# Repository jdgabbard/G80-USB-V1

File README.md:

# G80-USB V1
 G80-USB v1.0 SBC

The G80-USB Micro SBC.  The second iteration of the G80 Computer family, this computer made a change to it's communication by allowing for RS-232 or USB Serial interfaces to communicate with the computer.

The source code for the firmware can be found here: https://github.com/jdgabbard/z80-G-DOS

Or you can download previous version of the software in the downloads section of my website:  www.retrodepot.net

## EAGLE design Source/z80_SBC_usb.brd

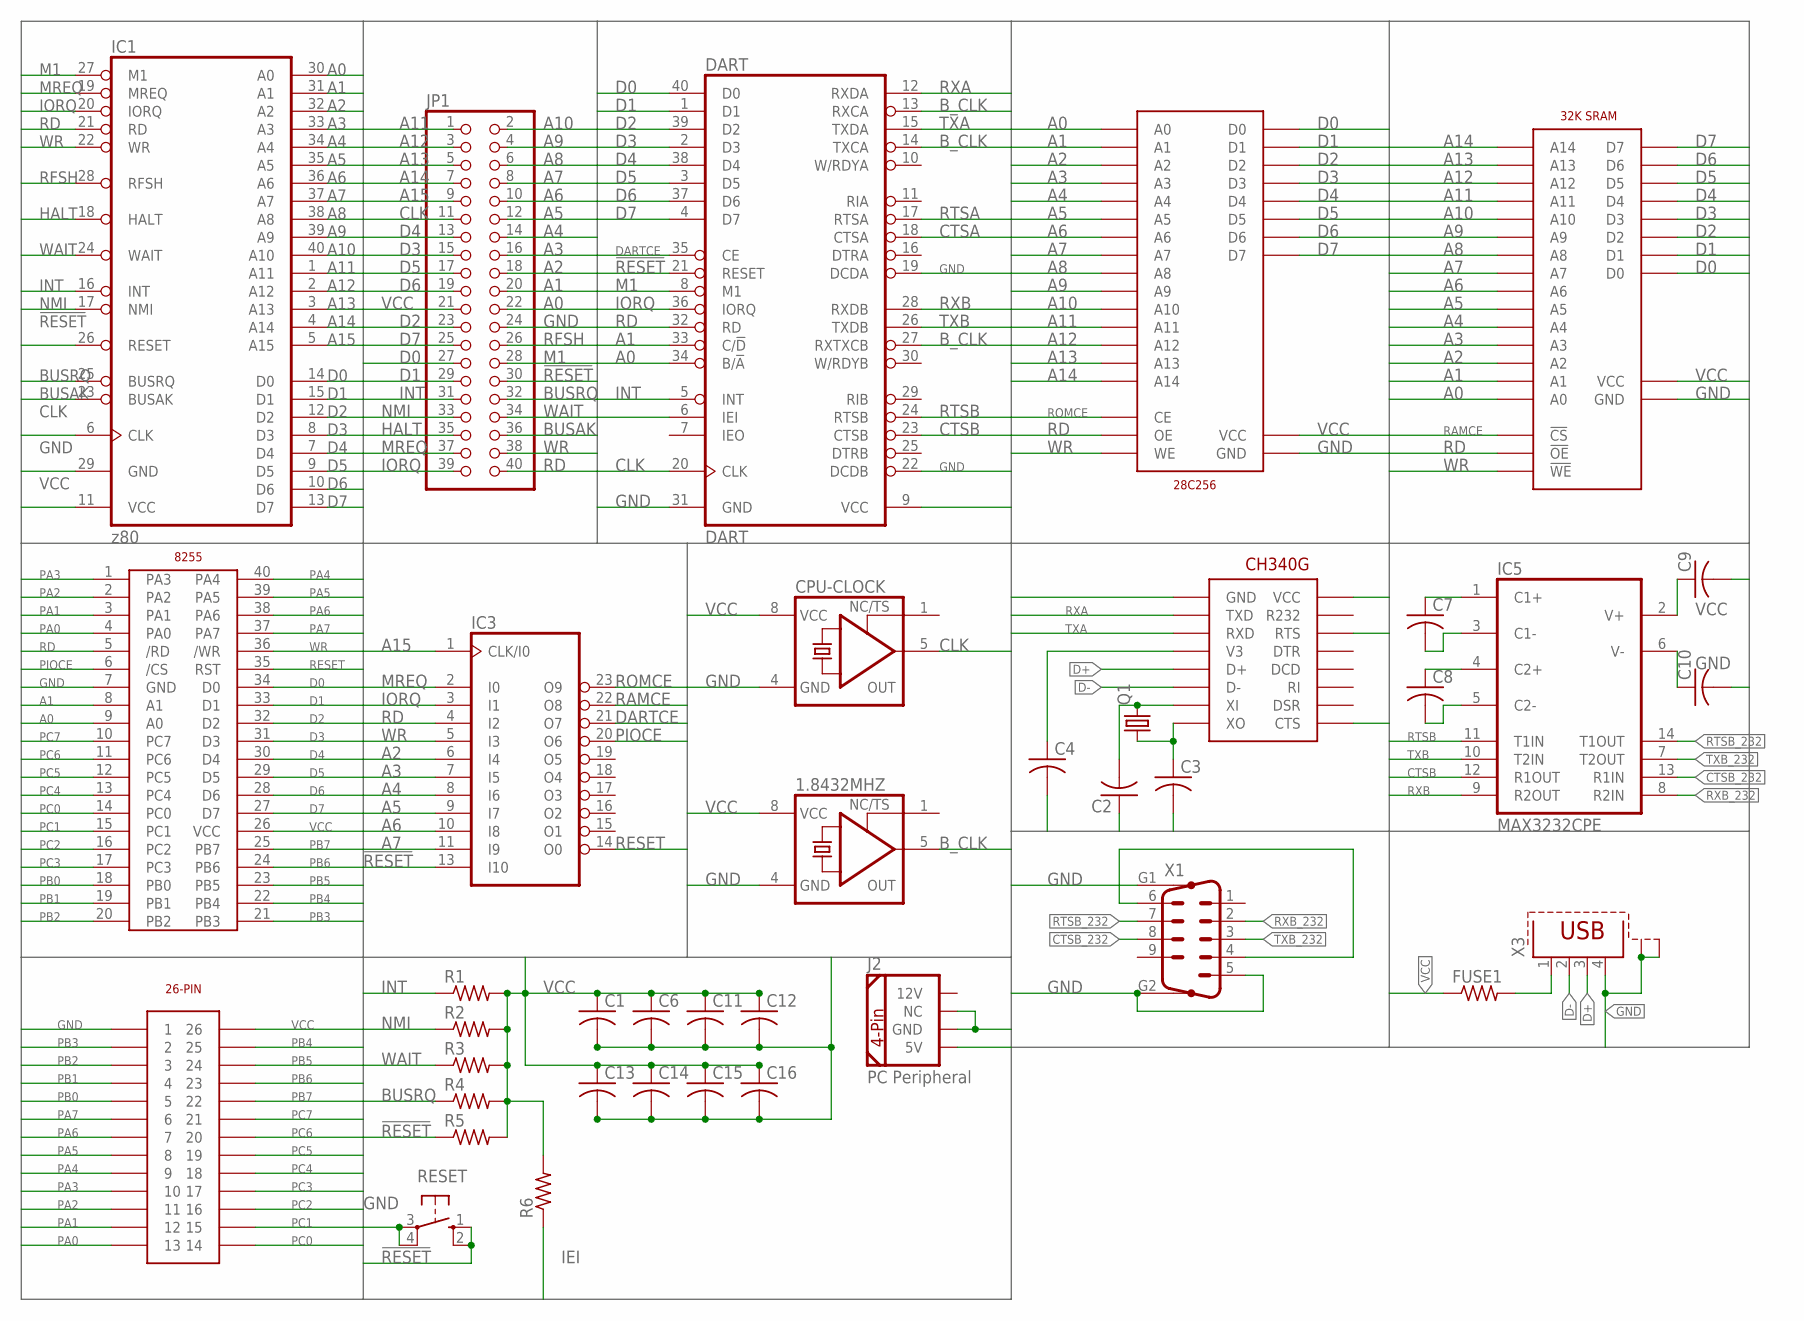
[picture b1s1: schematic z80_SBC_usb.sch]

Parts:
1.8432MHZ: XO-8; DIL08S
28C256: 28C256; DIP28
C1, C4, C6, C7, C8, C9, C10, C11, C12, C13, C14, C15, C16: C-USC0805; C0805
C2, C3: C-US050-024X044; C050-024X044
CPU-CLOCK: XO-8; DIL08S
DART: DART; DIL40
FUSE1: R-US_R1206W; R1206W
IC1: z80; DIL40
IC3: 22V10; DIL24-3
IC4: 8255
IC5: MAX3232CPE; DIL16
IC6: 32K SRAM; DIP28-300
IC7: CH340G; SO16
J1: SOCKET-DIP26
J2: PC Peripheral; COMPUTER-PERIPHERAL-POWER
JP1: PINHD-2X20; 2X20
Q1: CRYSTALHC49S; HC49/S
R1, R2, R3, R4, R5, R6: R-US_M0805; M0805
RESET: 10-XX; B3F-10XX
X1: M09HP
X3: PN61729-S

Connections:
!RESET: DART.21 (RESET), IC1.26 (RESET), IC3.13 (I10), JP1.30, R5.1, RESET.1 (S), RESET.2 (S1)
A0: 28C256.P$10 (A0), DART.34 (B/!A), IC1.30 (A0), IC4.9 (A0), IC6.P$10 (A0), JP1.22
A1: 28C256.P$9 (A1), DART.33 (C/!D), IC1.31 (A1), IC4.8 (A1), IC6.P$9 (A1), JP1.20
A2: 28C256.P$8 (A2), IC1.32 (A2), IC3.6 (I4), IC6.P$8 (A2), JP1.18
A3: 28C256.P$7 (A3), IC1.33 (A3), IC3.7 (I5), IC6.P$7 (A3), JP1.16
A4: 28C256.P$6 (A4), IC1.34 (A4), IC3.8 (I6), IC6.P$6 (A4), JP1.14
A5: 28C256.P$5 (A5), IC1.35 (A5), IC3.9 (I7), IC6.P$5 (A5), JP1.12
A6: 28C256.P$4 (A6), IC1.36 (A6), IC3.10 (I8), IC6.P$4 (A6), JP1.10
A7: 28C256.P$3 (A7), IC1.37 (A7), IC3.11 (I9), IC6.P$3 (A7), JP1.8
A8: 28C256.P$25 (A8), IC1.38 (A8), IC6.P$25 (A8), JP1.6
A9: 28C256.P$24 (A9), IC1.39 (A9), IC6.P$24 (A9), JP1.4
A10: 28C256.P$21 (A10), IC1.40 (A10), IC6.P$21 (A10), JP1.2
A11: 28C256.P$23 (A11), IC1.1 (A11), IC6.P$23 (A11), JP1.1
A12: 28C256.P$2 (A12), IC1.2 (A12), IC6.P$2 (A12), JP1.3
A13: 28C256.P$26 (A13), IC1.3 (A13), IC6.P$26 (A13), JP1.5
A14: 28C256.P$1 (A14), IC1.4 (A14), IC6.P$1 (A14), JP1.7
A15: IC1.5 (A15), IC3.1 (CLK/I0), JP1.9
BUSAK: IC1.23 (BUSAK), JP1.36
BUSRQ: IC1.25 (BUSRQ), JP1.32, R4.1
B_CLK: 1.8432MHZ.5 (OUT), DART.13 (RXCA), DART.14 (TXCA), DART.27 (RXTXCB)
CLK: CPU-CLOCK.5 (OUT), DART.20 (CLK), IC1.6 (CLK), JP1.11
CTSA: DART.18 (CTSA), IC7.14 (RTS)
CTSB: DART.23 (CTSB), IC5.12 (R1OUT)
CTSB_232: IC5.13 (R1IN), X1.8
D0: 28C256.P$11 (D0), DART.40 (D0), IC1.14 (D0), IC4.34 (D0), IC6.P$11 (D0), JP1.27
D1: 28C256.P$12 (D1), DART.1 (D1), IC1.15 (D1), IC4.33 (D1), IC6.P$12 (D1), JP1.29
D2: 28C256.P$13 (D2), DART.39 (D2), IC1.12 (D2), IC4.32 (D2), IC6.P$13 (D2), JP1.23
D3: 28C256.P$15 (D3), DART.2 (D3), IC1.8 (D3), IC4.31 (D3), IC6.P$15 (D3), JP1.15
D4: 28C256.P$16 (D4), DART.38 (D4), IC1.7 (D4), IC4.30 (D4), IC6.P$16 (D4), JP1.13
D5: 28C256.P$17 (D5), DART.3 (D5), IC1.9 (D5), IC4.29 (D5), IC6.P$17 (D5), JP1.17
D6: 28C256.P$18 (D6), DART.37 (D6), IC1.10 (D6), IC4.28 (D6), IC6.P$18 (D6), JP1.19
D7: 28C256.P$19 (D7), DART.4 (D7), IC1.13 (D7), IC4.27 (D7), IC6.P$19 (D7), JP1.25
D+: IC7.5 (D+), X3.3
D-: IC7.6 (D-), X3.2
DARTCE: DART.35 (CE), IC3.21 (O7)
GND: 1.8432MHZ.4 (GND), 28C256.P$14 (GND), C1.2, C2.1, C3.2, C4.2, C6.2, C10.2, C11.2, C12.2, C13.2, C14.2, C15.2, C16.2, CPU-CLOCK.4 (GND), DART.19 (DCDA), DART.22 (DCDB), DART.31 (GND), IC1.29 (GND), IC3.12 (GND), IC4.7 (GND), IC5.15 (GND), IC6.P$14 (GND), IC7.1 (GND), J1.P$1 (1), J2.GND, J2.NC, JP1.24, RESET.3, RESET.4 (P1), X1.5, X1.G1, X1.G2, X3.4, X3.S1, X3.S2
HALT: IC1.18 (HALT), JP1.35
IEI: DART.6 (IEI), R6.1
INT: DART.5 (INT), IC1.16 (INT), JP1.31, R1.1
IORQ: DART.36 (IORQ), IC1.20 (IORQ), IC3.3 (I1), JP1.39
M1: DART.8 (M1), IC1.27 (M1), JP1.28
MREQ: IC1.19 (MREQ), IC3.2 (I0), JP1.37
unnamed: C7.1, IC5.1 (C1+)
unnamed: C8.1, IC5.4 (C2+)
unnamed: C8.2, IC5.5 (C2-)
unnamed: C7.2, IC5.3 (C1-)
unnamed: C9.1, IC5.2 (V+)
unnamed: C10.1, IC5.6 (V-)
unnamed: C2.2, IC7.7 (XI), Q1.2
unnamed: C3.1, IC7.8 (XO), Q1.1
unnamed: FUSE1.2, X3.1
unnamed: C4.1, IC7.4 (V3)
unnamed: X1.4, X1.6
NMI: IC1.17 (NMI), JP1.33, R2.1
PA0: IC4.4 (PA0), J1.P$13 (13)
PA1: IC4.3 (PA1), J1.P$12 (12)
PA2: IC4.2 (PA2), J1.P$11 (11)
PA3: IC4.1 (PA3), J1.P$10 (10)
PA4: IC4.40 (PA4), J1.P$9 (9)
PA5: IC4.39 (PA5), J1.P$8 (8)
PA6: IC4.38 (PA6), J1.P$7 (7)
PA7: IC4.37 (PA7), J1.P$6 (6)
PB0: IC4.18 (PB0), J1.P$5 (5)
PB1: IC4.19 (PB1), J1.P$4 (4)
PB2: IC4.20 (PB2), J1.P$3 (3)
PB3: IC4.21 (PB3), J1.P$2 (2)
PB4: IC4.22 (PB4), J1.P$25 (25)
PB5: IC4.23 (PB5), J1.P$24 (24)
PB6: IC4.24 (PB6), J1.P$23 (23)
PB7: IC4.25 (PB7), J1.P$22 (22)
PC0: IC4.14 (PC0), J1.P$14 (14)
PC1: IC4.15 (PC1), J1.P$15 (15)
PC2: IC4.16 (PC2), J1.P$16 (16)
PC3: IC4.17 (PC3), J1.P$17 (17)
PC4: IC4.13 (PC4), J1.P$18 (18)
PC5: IC4.12 (PC5), J1.P$19 (19)
PC6: IC4.11 (PC6), J1.P$20 (20)
PC7: IC4.10 (PC7), J1.P$21 (21)
PIOCE: IC3.20 (O6), IC4.6 (/CS)
RAMCE: IC3.22 (O8), IC6.P$20 (!CS)
RD: 28C256.P$22 (OE), DART.32 (RD), IC1.21 (RD), IC3.4 (I2), IC4.5 (/RD), IC6.P$22 (!OE), JP1.40
RESET: IC3.14 (O0), IC4.35 (RST)
RFSH: IC1.28 (RFSH), JP1.26
ROMCE: 28C256.P$20 (CE), IC3.23 (O9)
RTSA: DART.17 (RTSA), IC7.9 (CTS)
RTSB: DART.24 (RTSB), IC5.11 (T1IN)
RTSB_232: IC5.14 (T1OUT), X1.7
RXA: DART.12 (RXDA), IC7.2 (TXD)
RXB: DART.28 (RXDB), IC5.9 (R2OUT)
RXB_232: IC5.8 (R2IN), X1.2
TXA: DART.15 (TXDA), IC7.3 (RXD)
TXB: DART.26 (TXDB), IC5.10 (T2IN)
TXB_232: IC5.7 (T2OUT), X1.3
VCC: 1.8432MHZ.8 (VCC), 28C256.P$28 (VCC), C1.1, C6.1, C9.2, C11.1, C12.1, C13.1, C14.1, C15.1, C16.1, CPU-CLOCK.8 (VCC), DART.9 (VCC), FUSE1.1, IC1.11 (VCC), IC3.24 (VCC), IC4.26 (VCC), IC5.16 (VCC), IC6.P$28 (VCC), IC7.16 (VCC), J1.P$26 (26), J2.5V, JP1.21, R1.2, R2.2, R3.2, R4.2, R5.2, R6.2
WAIT: IC1.24 (WAIT), JP1.34, R3.1
WR: 28C256.P$27 (WE), IC1.22 (WR), IC3.5 (I3), IC4.36 (/WR), IC6.P$27 (!WE), JP1.38

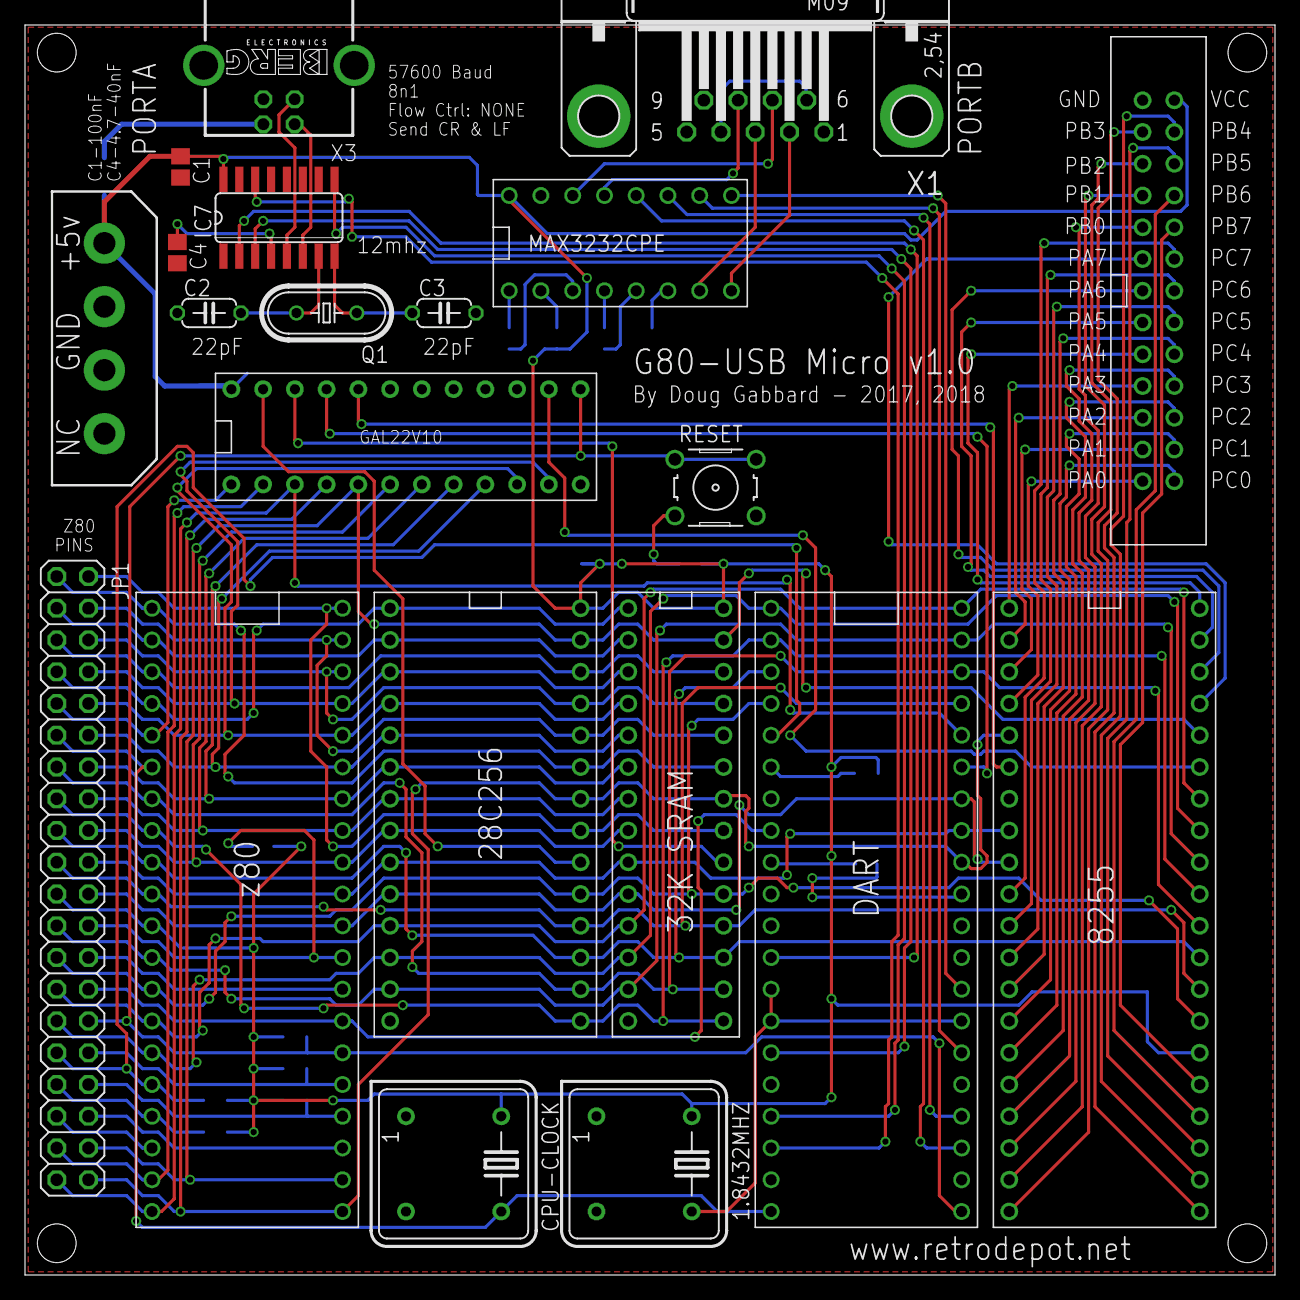
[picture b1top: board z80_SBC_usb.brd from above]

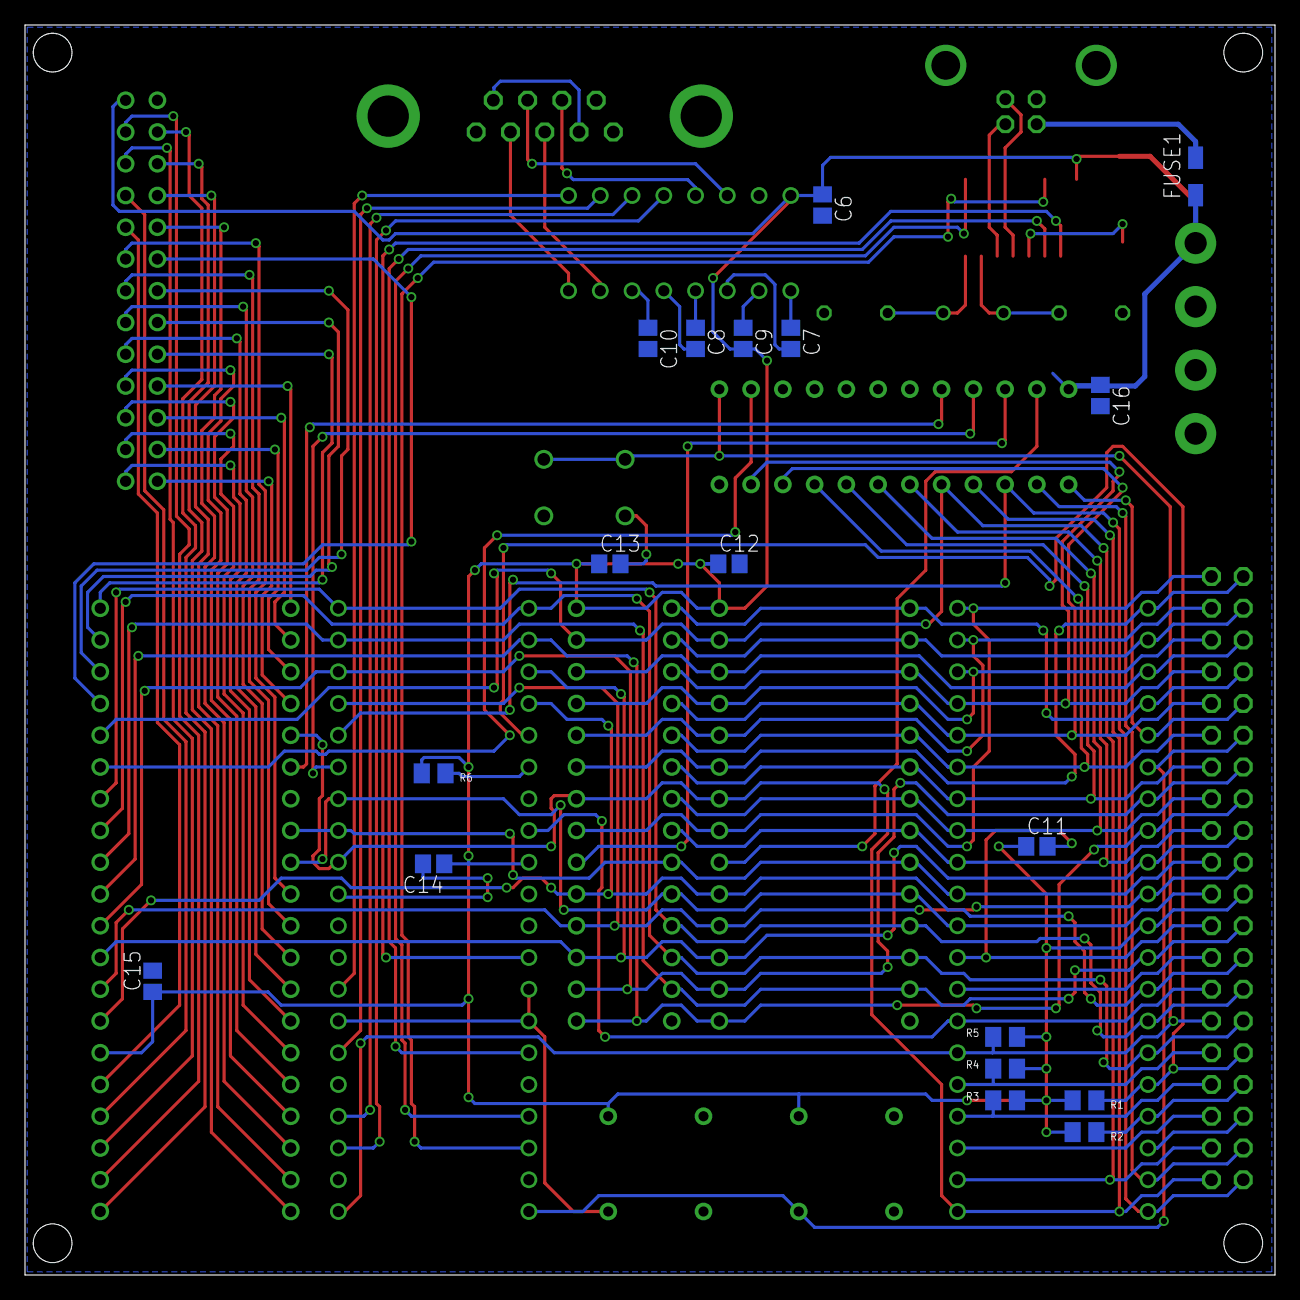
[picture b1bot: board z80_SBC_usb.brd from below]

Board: 2 copper layers, 100.0 x 100.0 mm, 39 parts (18 on the bottom side), 96 nets.

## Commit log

2022-02-26 Initial Upload

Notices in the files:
parts and their libraries:
SparkFun-Connectors: Licensing: Creative Commons ShareAlike 4.0 International - https://creativecommons.org/licenses/by-sa/4.0
